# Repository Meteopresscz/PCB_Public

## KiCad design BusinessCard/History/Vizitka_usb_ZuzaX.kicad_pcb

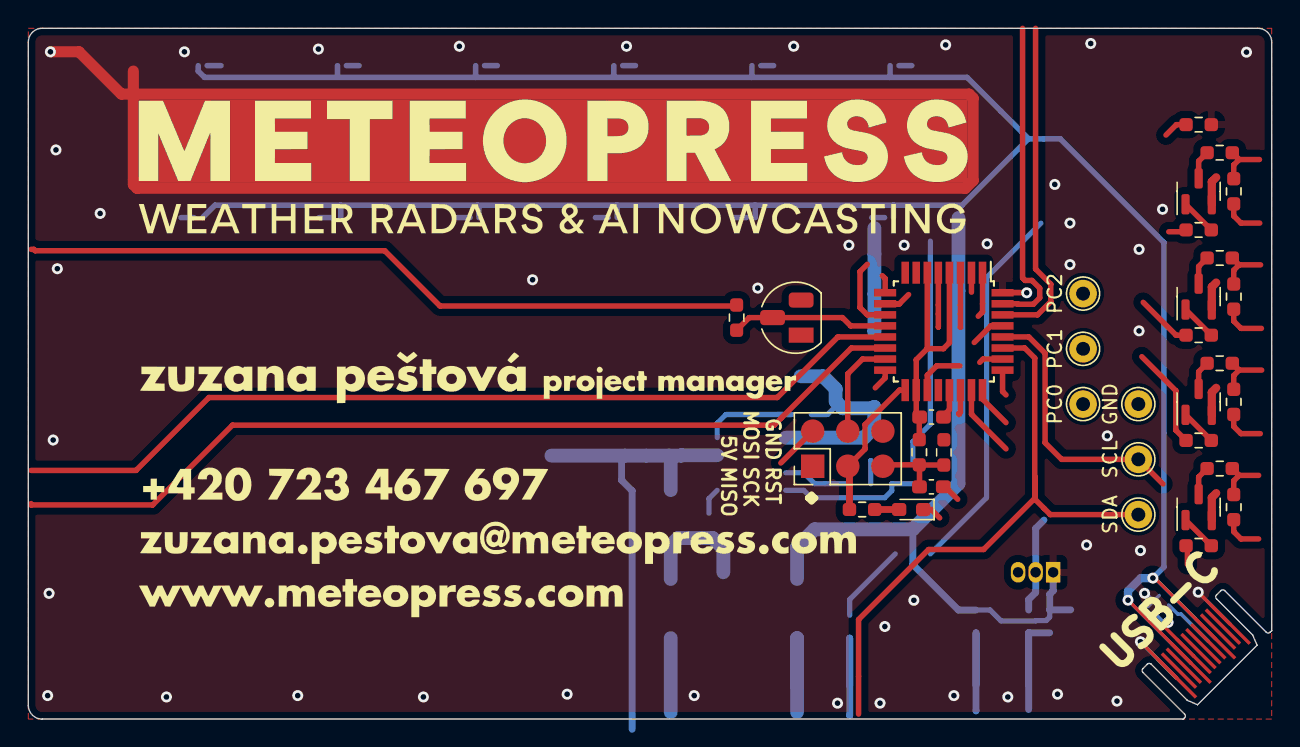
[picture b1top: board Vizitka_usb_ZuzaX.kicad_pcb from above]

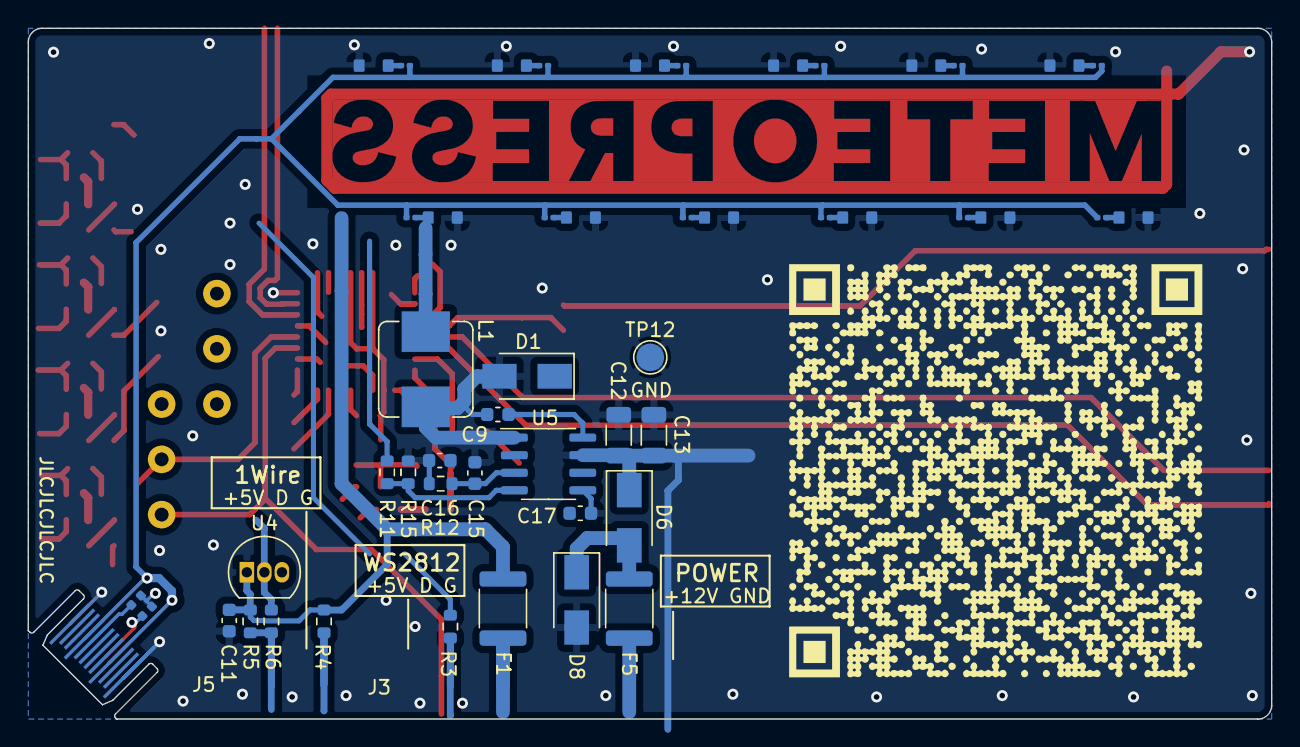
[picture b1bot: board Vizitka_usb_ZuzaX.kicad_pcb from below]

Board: 2 copper layers, 90.0 x 50.0 mm, 84 parts (49 on the bottom side), 16 nets.

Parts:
C9, C11: 100n; C_0603_1608Metric
C12, C13: 4u7/50V; C_1206_3216Metric
C14: 1u; C_0603_1608Metric_Pad1.08x0.95mm_HandSolder
C15, C17: 8.2n; C_0603_1608Metric
C16: 100n; C_0603_1608Metric_Pad1.08x0.95mm_HandSolder
C16#2: 22n; C_0603_1608Metric
D1: LED; LED_0603_1608Metric_Pad1.05x0.95mm_HandSolder
D1#2, D2, D3, D4, D5, D6, D7, D8, D9, D10, D11, D12: LED; D_0802_side_woSilk
D1#3: SS14; D_SMA
D6#2: D_Schottky; D_SMA
D8#2: TVS; D_SMA
F1: 0.5A; Fuse_1812_4532Metric
F5: 1A; Fuse_1812_4532Metric
J1: AVR-ISP-6; PinHeader_2x03_P2.54mm_Vertical
J2: USB_C_Receptacle; PCB-USB-C_straight
J3: Conn_01x01; MeteopressLogo_Bare_Inv_60x6
L1: 47u; L_Bourns_SRP7028A_7.3x6.6mm
Q1, Q3, Q5, Q11: MMBT3904; SOT-23
R1, R2, R3, R4#2, R5, R6, R7, R8#2, R9#2, R10, R11#2, R12#2: 330; R_0201_woSilk
R3#2, R6#2: 330R; R_0603_1608Metric
R4: 150R; R_0603_1608Metric
R5#2: 22k; R_0603_1608Metric
R8, R11, R14: 4k7; R_0603_1608Metric_Pad0.98x0.95mm_HandSolder
R9, R22, R30: 10k; R_0603_1608Metric_Pad0.98x0.95mm_HandSolder
R11#3: 10k; R_0603_1608Metric
R12: 100R; R_0603_1608Metric
R15: 1k8; R_0603_1608Metric
R20, R24, R28, R40: 100k; R_0603_1608Metric_Pad0.98x0.95mm_HandSolder
R21, R25, R26, R29, R37, R41, R42: 47k; R_0603_1608Metric_Pad0.98x0.95mm_HandSolder
R42#2, R43: 5k1; D_0402_woSilk
TP2: SCL; TestPoint_THTPad_D2.0mm_Drill1.0mm
TP3: SDA; TestPoint_THTPad_D2.0mm_Drill1.0mm
TP12, TP14: GND; TestPoint_THTPad_D2.0mm_Drill1.0mm
TP27: PC0; TestPoint_THTPad_D2.0mm_Drill1.0mm
TP28: PC1; TestPoint_THTPad_D2.0mm_Drill1.0mm
TP29: PC2; TestPoint_THTPad_D2.0mm_Drill1.0mm
U1: ATmega328P-AU; TQFP-32_7x7mm_P0.8mm
U2: DS18B20; TO-92_HandSolder
U4: DS18B20; TO-92_Inline
U5: TPS54331; SOIC-8_3.9x4.9mm_P1.27mm

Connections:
+5V: C11.1, F1.1, J2.A4 (VBUS), J2.A9 (VBUS), J2.B4 (VBUS), J2.B9 (VBUS), L1.2, R1.2, R2.2, R3.2, R4.1, R4#2.2, R5.2, R5#2.1, R6.2, R7.2, R8#2.2, R9#2.2, R10.2, R11#2.2, R11#3.1, R12#2.2, U4.3 (VDD)
GND: C11.2, C12.2, C13.2, C15.2, C16#2.2, C17.2, D1#2.1 (K), D1#3.2 (A), D2.1 (K), D3.1 (K), D4.1 (K), D5.1 (K), D6.1 (K), D7.1 (K), D8.1 (K), D8#2.2 (A), D9.1 (K), D10.1 (K), D11.1 (K), D12.1 (K), J2.A1 (GND), J2.A12 (GND), J2.B1 (GND), J2.B12 (GND), R15.2, R37.2, R42#2.1, R43.1, TP12.1, U1.32 (PD2), U4.1 (GND), U5.7 (GND)
unnamed: D1#2.2 (A), R1.1
unnamed: D2.2 (A), R2.1
unnamed: D3.2 (A), R3.1
unnamed: D4.2 (A), R4#2.1
unnamed: D5.2 (A), R5.1
unnamed: D6.2 (A), D6#2.2 (A), D8#2.1 (K), F5.2, R6.1
unnamed: D7.2 (A), R7.1
unnamed: D8.2 (A), R8#2.1
unnamed: D9.2 (A), R9#2.1
unnamed: D10.2 (A), R10.1
unnamed: D11.2 (A), R11#2.1
unnamed: D12.2 (A), R12#2.1
unnamed: J2.A5 (CC1), R43.2
unnamed: J2.B5 (CC2), R42#2.2

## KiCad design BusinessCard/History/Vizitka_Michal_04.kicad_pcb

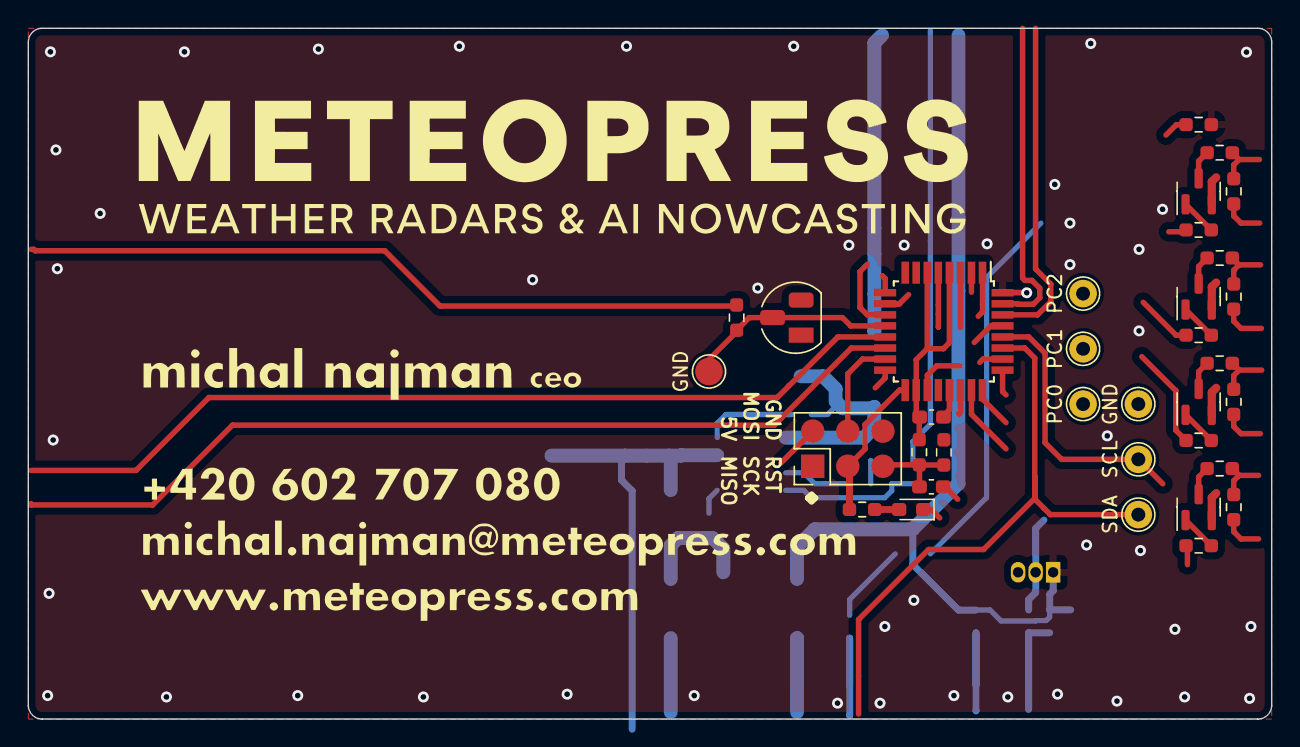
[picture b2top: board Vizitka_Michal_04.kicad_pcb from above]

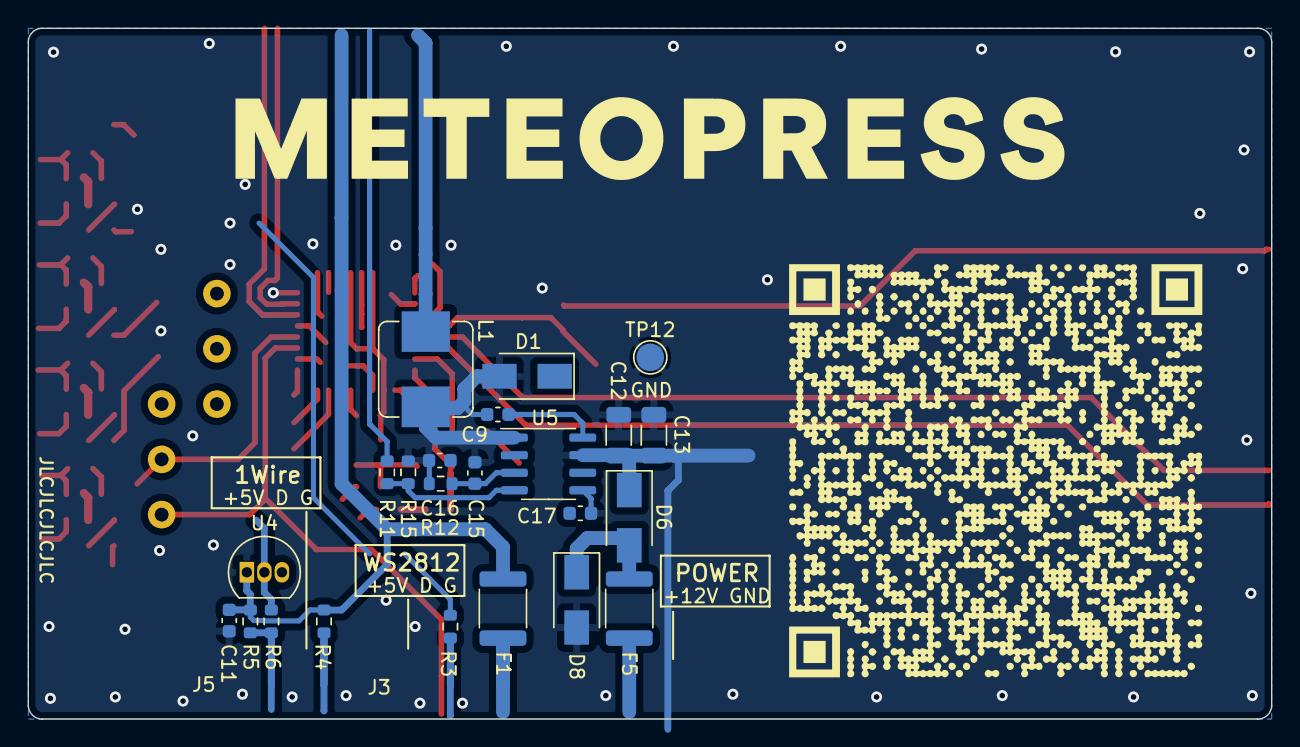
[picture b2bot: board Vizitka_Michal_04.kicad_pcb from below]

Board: 2 copper layers, 90.0 x 50.0 mm, 57 parts (23 on the bottom side), 3 nets.

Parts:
C9, C11: 100n; C_0603_1608Metric
C12, C13: 4u7/50V; C_1206_3216Metric
C14: 1u; C_0603_1608Metric_Pad1.08x0.95mm_HandSolder
C15, C17: 8.2n; C_0603_1608Metric
C16: 100n; C_0603_1608Metric_Pad1.08x0.95mm_HandSolder
C16#2: 22n; C_0603_1608Metric
D1: LED; LED_0603_1608Metric_Pad1.05x0.95mm_HandSolder
D1#2: SS14; D_SMA
D6: D_Schottky; D_SMA
D8: TVS; D_SMA
F1: 0.5A; Fuse_1812_4532Metric
F5: 1A; Fuse_1812_4532Metric
J1: AVR-ISP-6; PinHeader_2x03_P2.54mm_Vertical
L1: 47u; L_Bourns_SRP7028A_7.3x6.6mm
Q1, Q3, Q5, Q11: MMBT3904; SOT-23
R3, R6: 330R; R_0603_1608Metric
R4: 150R; R_0603_1608Metric
R5: 22k; R_0603_1608Metric
R8, R11, R14: 4k7; R_0603_1608Metric_Pad0.98x0.95mm_HandSolder
R9, R22, R30: 10k; R_0603_1608Metric_Pad0.98x0.95mm_HandSolder
R11#2: 10k; R_0603_1608Metric
R12: 100R; R_0603_1608Metric
R15: 1k8; R_0603_1608Metric
R20, R24, R28, R40: 100k; R_0603_1608Metric_Pad0.98x0.95mm_HandSolder
R21, R25, R26, R29, R37, R41, R42: 47k; R_0603_1608Metric_Pad0.98x0.95mm_HandSolder
TP2: SCL; TestPoint_THTPad_D2.0mm_Drill1.0mm
TP3: SDA; TestPoint_THTPad_D2.0mm_Drill1.0mm
TP12, TP14, TP18: GND; TestPoint_THTPad_D2.0mm_Drill1.0mm
TP27: PC0; TestPoint_THTPad_D2.0mm_Drill1.0mm
TP28: PC1; TestPoint_THTPad_D2.0mm_Drill1.0mm
TP29: PC2; TestPoint_THTPad_D2.0mm_Drill1.0mm
U1: ATmega328P-AU; TQFP-32_7x7mm_P0.8mm
U2: DS18B20; TO-92_HandSolder
U4: DS18B20; TO-92_Inline
U5: TPS54331; SOIC-8_3.9x4.9mm_P1.27mm

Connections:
+5V: C11.1, F1.1, L1.2, R4.1, R5.1, R11#2.1, U4.3 (VDD)
GND: C11.2, C12.2, C13.2, C15.2, C16#2.2, C17.2, D1#2.2 (A), D8.2 (A), R15.2, R37.2, TP12.1, U1.32 (PD2), U4.1 (GND), U5.7 (GND)
unnamed: D6.2 (A), D8.1 (K), F5.2

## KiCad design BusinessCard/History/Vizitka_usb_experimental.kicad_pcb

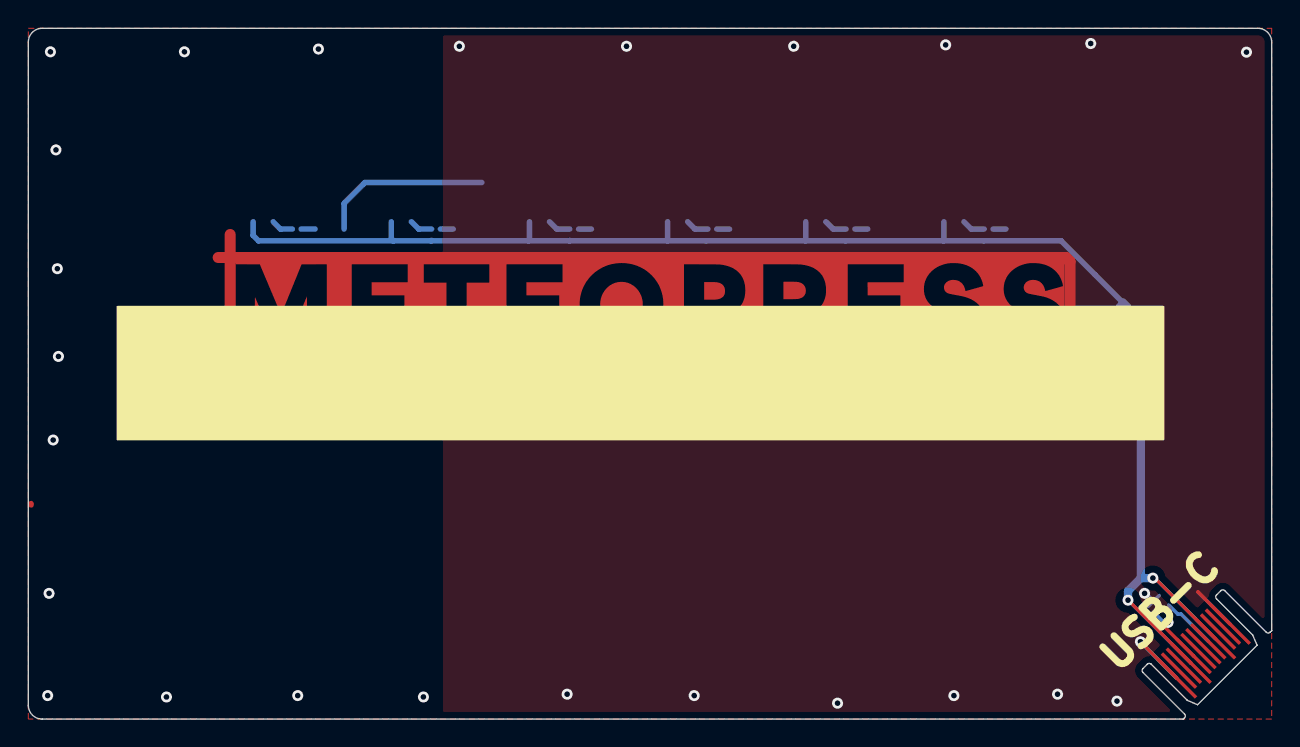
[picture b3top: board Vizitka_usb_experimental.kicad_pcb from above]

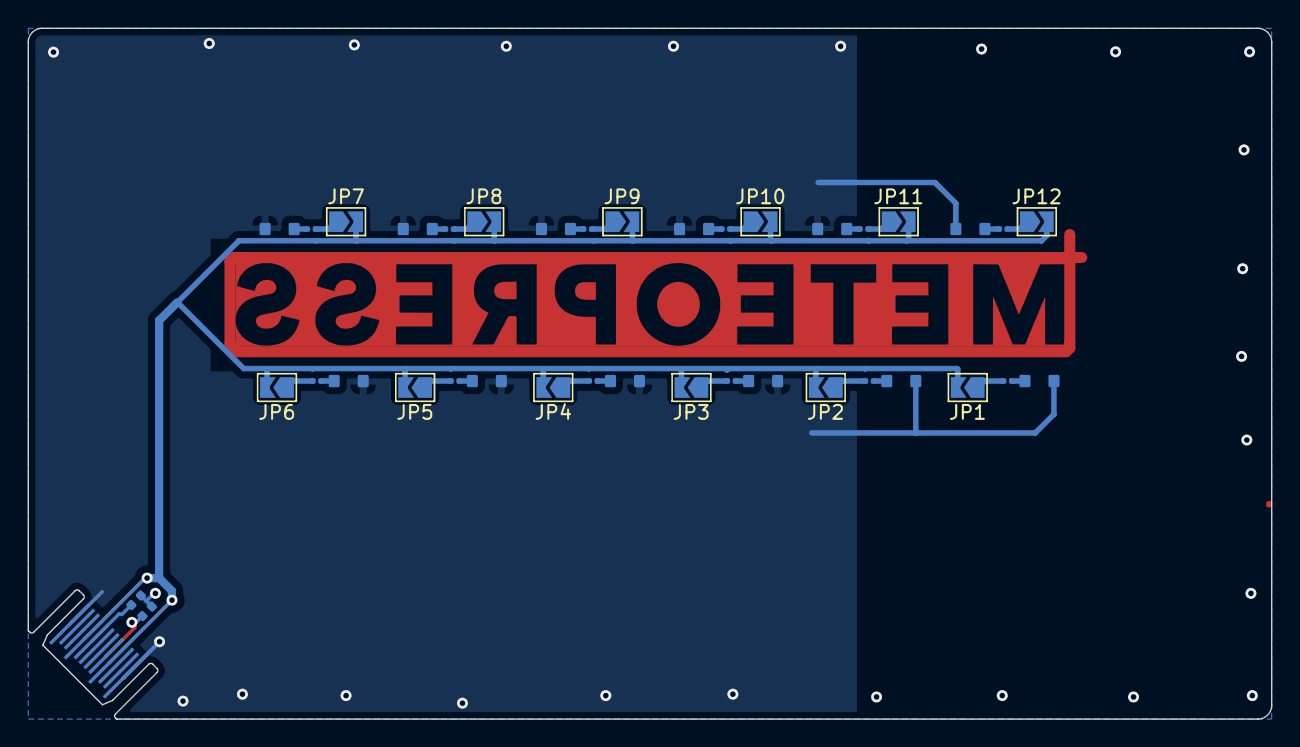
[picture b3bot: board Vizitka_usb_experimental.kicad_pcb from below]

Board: 2 copper layers, 90.0 x 50.0 mm, 40 parts (38 on the bottom side), 28 nets.

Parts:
D1, D2, D3, D4, D5, D6, D7, D8, D9, D10, D11, D12: LED; D_0802_side_woSilk
J2: USB_C_Receptacle; PCB-USB-C_straight
J3: Conn_01x01; MeteopressLogo_Bare_Inv_60x6
JP1, JP2, JP3, JP4, JP5, JP6, JP7, JP8, JP9, JP10, JP11, JP12: Jumper_2_Open; SolderJumper-2_P1.3mm_Open_TrianglePad1.0x1.5mm
R1, R2, R3, R4, R5, R6, R7, R8, R9, R10, R11, R12: 330; R_0201_woSilk
R42, R43: 5k1; D_0402_woSilk

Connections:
+5V: J2.A4 (VBUS), J2.A9 (VBUS), J2.B4 (VBUS), J2.B9 (VBUS), JP1.2 (B), JP2.2 (B), JP3.2 (B), JP4.2 (B), JP5.2 (B), JP6.2 (B), JP7.2 (B), JP8.2 (B), JP9.2 (B), JP10.2 (B), JP11.2 (B), JP12.2 (B)
GND: D1.1 (K), D2.1 (K), D3.1 (K), D4.1 (K), D5.1 (K), D6.1 (K), D7.1 (K), D8.1 (K), D9.1 (K), D10.1 (K), D11.1 (K), D12.1 (K), J2.A1 (GND), J2.A12 (GND), J2.B1 (GND), J2.B12 (GND), R42.1, R43.1
unnamed: D1.2 (A), R1.1
unnamed: D2.2 (A), R2.1
unnamed: D3.2 (A), R3.1
unnamed: D4.2 (A), R4.1
unnamed: D5.2 (A), R5.1
unnamed: D6.2 (A), R6.1
unnamed: D7.2 (A), R7.1
unnamed: D8.2 (A), R8.1
unnamed: D9.2 (A), R9.1
unnamed: D10.2 (A), R10.1
unnamed: D11.2 (A), R11.1
unnamed: D12.2 (A), R12.1
unnamed: J2.A5 (CC1), R43.2
unnamed: J2.B5 (CC2), R42.2
unnamed: JP1.1 (A), R1.2
unnamed: JP2.1 (A), R2.2
unnamed: JP3.1 (A), R3.2
unnamed: JP4.1 (A), R4.2
unnamed: JP5.1 (A), R5.2
unnamed: JP6.1 (A), R6.2
unnamed: JP7.1 (A), R7.2
unnamed: JP8.1 (A), R8.2
unnamed: JP9.1 (A), R9.2
unnamed: JP10.1 (A), R10.2
unnamed: JP11.1 (A), R11.2
unnamed: JP12.1 (A), R12.2

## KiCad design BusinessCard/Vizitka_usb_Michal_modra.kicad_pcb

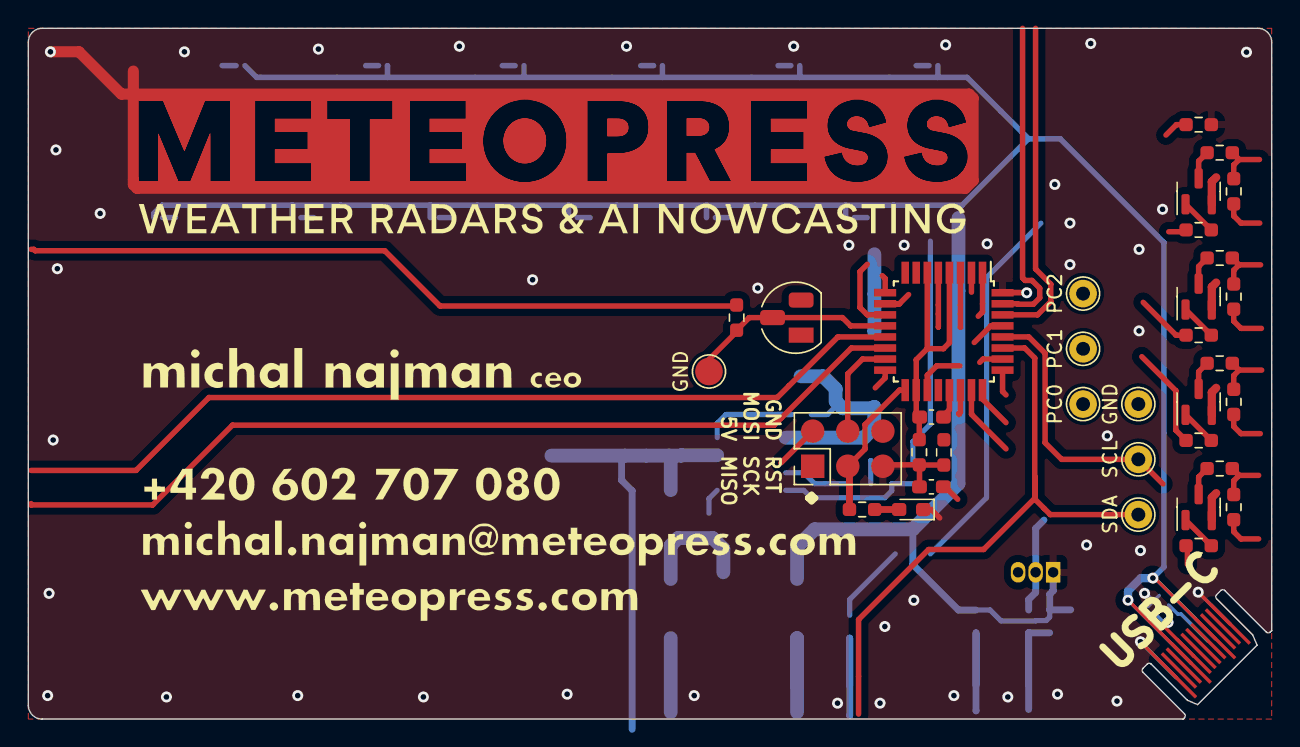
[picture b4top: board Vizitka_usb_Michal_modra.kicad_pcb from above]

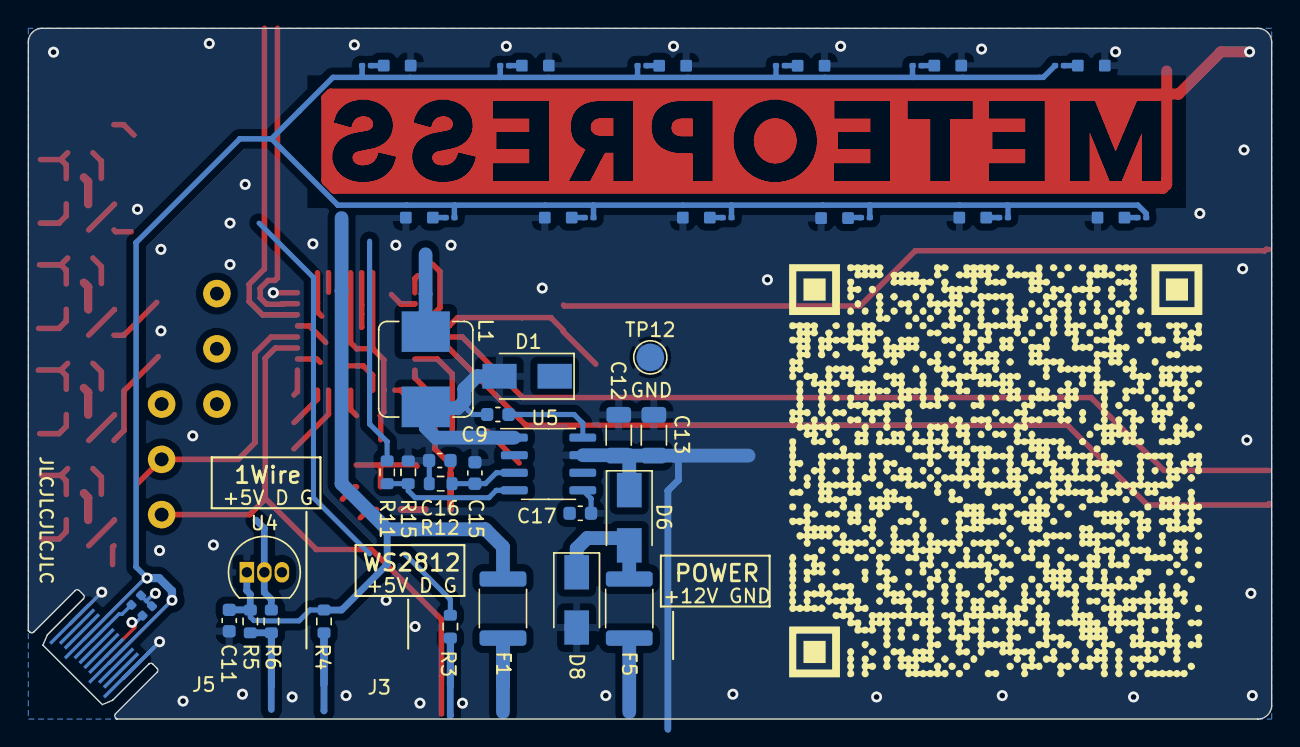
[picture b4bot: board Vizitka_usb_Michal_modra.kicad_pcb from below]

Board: 2 copper layers, 90.0 x 50.0 mm, 86 parts (49 on the bottom side), 17 nets.

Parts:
C9, C11: 100n; C_0603_1608Metric
C12, C13: 4u7/50V; C_1206_3216Metric
C14: 1u; C_0603_1608Metric_Pad1.08x0.95mm_HandSolder
C15, C17: 8.2n; C_0603_1608Metric
C16: 100n; C_0603_1608Metric_Pad1.08x0.95mm_HandSolder
C16#2: 22n; C_0603_1608Metric
D1: LED; LED_0603_1608Metric_Pad1.05x0.95mm_HandSolder
D1#2: SS14; D_SMA
D6: D_Schottky; D_SMA
D8: TVS; D_SMA
D101, D102, D103, D104, D105, D106, D107, D108, D109, D110, D111, D112: LED; D_0802_side_woSilk_C965872
F1: 0.5A; Fuse_1812_4532Metric
F5: 1A; Fuse_1812_4532Metric
J1: USB_B_Micro; PinHeader_2x03_P2.54mm_Vertical
J2: USB_C_Receptacle; PCB-USB-C_straight
J3, J3#2: Conn_01x01; MeteopressLogo_Bare_Inv_60x6
L1: 47u; L_Bourns_SRP7028A_7.3x6.6mm
Q1, Q3, Q5, Q11: MMBT3904; SOT-23
R3, R6: 330R; R_0603_1608Metric
R4: 150R; R_0603_1608Metric
R5: 22k; R_0603_1608Metric
R8, R11, R14: 4k7; R_0603_1608Metric_Pad0.98x0.95mm_HandSolder
R9, R22, R30: 10k; R_0603_1608Metric_Pad0.98x0.95mm_HandSolder
R11#2: 10k; R_0603_1608Metric
R12: 100R; R_0603_1608Metric
R15: 1k8; R_0603_1608Metric
R20, R24, R28, R40: 100k; R_0603_1608Metric_Pad0.98x0.95mm_HandSolder
R21, R25, R26, R29, R37, R41, R42: 47k; R_0603_1608Metric_Pad0.98x0.95mm_HandSolder
R101, R102, R103, R104, R105, R106, R107, R108, R109, R110, R111, R112: 120; R_0201_woSilk
R142, R143: 5k1; D_0402_woSilk
TP2: SCL; TestPoint_THTPad_D2.0mm_Drill1.0mm
TP3: SDA; TestPoint_THTPad_D2.0mm_Drill1.0mm
TP12, TP14, TP18: GND; TestPoint_THTPad_D2.0mm_Drill1.0mm
TP27: PC0; TestPoint_THTPad_D2.0mm_Drill1.0mm
TP28: PC1; TestPoint_THTPad_D2.0mm_Drill1.0mm
TP29: PC2; TestPoint_THTPad_D2.0mm_Drill1.0mm
U1: ATmega328P-AU; TQFP-32_7x7mm_P0.8mm
U2: DS18B20; TO-92_HandSolder
U4: DS18B20; TO-92_Inline
U5: TPS54331; SOIC-8_3.9x4.9mm_P1.27mm

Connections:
+5V: C11.1, F1.1, J1.1 (VBUS), J2.A4 (VBUS), J2.A9 (VBUS), J2.B4 (VBUS), J2.B9 (VBUS), L1.2, R4.1, R5.1, R11#2.1, R101.2, R102.2, R103.2, R104.2, R105.2, R106.2, R107.2, R108.2, R109.2, R110.2, R111.2, R112.2, U4.3 (VDD)
GND: C11.2, C12.2, C13.2, C15.2, C16#2.2, C17.2, D1#2.2 (A), D8.2 (A), D101.1 (K), D102.1 (K), D103.1 (K), D104.1 (K), D105.1 (K), D106.1 (K), D107.1 (K), D108.1 (K), D109.1 (K), D110.1 (K), D111.1 (K), D112.1 (K), J1.5 (GND), J2.A1 (GND), J2.A12 (GND), J2.B1 (GND), J2.B12 (GND), R15.2, R37.2, R142.1, R143.1, TP12.1, U1.32 (PD2), U4.1 (GND), U5.7 (GND)
unnamed: D6.2 (A), D8.1 (K), F5.2
unnamed: D101.2 (A), R101.1
unnamed: D102.2 (A), R102.1
unnamed: D103.2 (A), R103.1
unnamed: D104.2 (A), R104.1
unnamed: D105.2 (A), R105.1
unnamed: D106.2 (A), R106.1
unnamed: D107.2 (A), R107.1
unnamed: D108.2 (A), R108.1
unnamed: D109.2 (A), R109.1
unnamed: D110.2 (A), R110.1
unnamed: D111.2 (A), R111.1
unnamed: D112.2 (A), R112.1
unnamed: J2.A5 (CC1), R143.2
unnamed: J2.B5 (CC2), R142.2

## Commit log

2022-11-23 Init commit - added BusinessCard and NotePad PCBs
2023-10-13 Added aditional businesscards - Zuza, MichalModra...Actual Tapeout 2023-08-24, but repaired connection!
